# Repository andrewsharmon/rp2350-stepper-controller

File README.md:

# RP2350 coordinated stepper controller

> **Work in progress.** Firmware runs on a Raspberry Pi Pico 2 bench setup.
> The custom board designs are an **unreviewed feasibility first pass**:
> schematics only, no PCB layout, not checked against datasheets or built.
> Don't fabricate them as-is.

A very low-cost, compact controller for up to **10 small stepper motors** (8 mm
micro steppers, 28BYJ-48 converted to bipolar, about 0.2 A per coil or less).
It's aimed at kinetic art first, then lab and robotics use.

There are no stepper-driver ICs. The RP2350 generates sine-PWM microstepping
itself (voltage mode), using PIO state machines fed by DMA, into cheap
DRV8833-class dual H-bridges (AT8833).

## Status

| # | Milestone | State |
|---|---|---|
| 1 | Hardware spec and KiCad schematics for all three boards | first pass, **not reviewed** (open part picks in [hardware/README.md](hardware/README.md)) |
| 2 | One motor: sine PWM via PIO + DMA | done, verified on hardware |
| 3 | 10-axis PWM, ADC monitor, e-stop/button ladder, WS2812 | done on Pico 2; ladder buttons not yet bench-wired |
| 4 | Trajectory generators and profiles, jog modes, telemetry | done (text telemetry; binary framing comes with milestone 5) |
| 5 | Coordinated groups and planner, USB protocol, host tool | done |
| 6 | I²C target, cam/LED shows, flash config, standalone mode | done; I²C target written for the RP2354B board but **untested** (no free pins or I²C master on the bench) |
| 7 | PCB layout, fab, bring-up of the board stack | |

What works today (measured on a Pico 2 + DRV8833 + 8 mm stepper):

- **PWM:** 20 kHz, four-segment H-bridge PWM with slow-decay brake off-time and 1/256-step sine microstepping. Duties below the driver's 0.5 µs minimum pulse are error-diffused.
- **10 axes:** each has its own position, velocity or jog mode on a 1 kHz trajectory tick. Drive amplitude depends on speed, with lower holding current at standstill. Core 1 is about 33-35% loaded, core 0 about 0.5%.
- **Coordinated groups:** up to 4 groups, each owning a set of axes. A group follows a queue of straight lines and arcs in joint space, with every axis starting and finishing together. Lookahead keeps it moving through gentle corners and chord-split arcs, and no axis exceeds its own limits. On the Pico 2, a 300-step-radius circle ran at a constant 800 steps/s and closed exactly.
- **Shows:** keyframe tracks for axes and LED pixels on one timeline, written as JSON, compiled and uploaded to one of 4 flash slots. Axes pass exactly through every keyframe (played as PVT), LED colours fade between keys, and shows can loop. A show is refused if any segment would exceed an axis's speed or acceleration limit. On the Pico 2, a looping 10-axis wave with 9 LED tracks hit all 360 keyframes checked exactly over 2.5 loops.
- **Built-in programs:** 12 looping motion patterns for a row of linear actuators (breathe, travel, standing, ripple, seesaw, zipper, domino, stairs, scan, chase, interference, drift), ±1000 full steps about position 0, all within the default limits (1500 steps/s, 2000 steps/s²). They run along the board's row of connectors, which on single_sh_proto is 5 6 7 8 9 10 1 2 3 4 from the far end to the USB end. They play through the show player as PVT streams, warming up from rest at their first pose. Position 0 is the power-up position, so power up with the actuators mid-stroke (or zero them there with `z`). `prog list`, `prog <n>`, `prog stop` on the console.
- **Standalone mode:** the buttons step through the built-in programs, then the stored shows, with no computer attached. Btn1 clears a latched stop once the e-stop is closed again, or starts / stops the selected entry; Btn2 selects the next one, switching to it if one is playing (the axes stop, then the new one starts). For 1.5 s after a press the axis LEDs show the entry's number as a bar: amber for programs 1-10, cyan for 11-12, magenta for shows. A boot program or show (`boot p<n>` / `boot <n>`, then `save`) starts at power-up.
- **Configuration in flash:** per-axis limits, motion profile, automatic amplitude curve (run low/high, hold, corner speeds) and wiring fixes (reverse direction, swap coils) survive power cycles. Two sectors are written alternately with a generation counter and CRC, so an interrupted save keeps the previous configuration.
- **Streamed PVT:** the host sends position/velocity/time points, and each axis follows a cubic through them. A 10-axis wave streamed at 20 ms per point tracked the ideal curve within 0.0005 steps. Running out of points while moving brakes safely.
- **Telemetry:** up to 1 kHz with selectable axes and fields (position, speed, mode, amplitude, PVT queue, plus motor voltage, ladder, stop state and the last applied command). Each line is numbered so a host can detect drops. Event lines report finished moves, PVT underruns and stops. At 1 kHz with every field on 10 axes, no lines were dropped and core 0 was 39% busy.
- **Electronic cams:** an axis can follow a cam table, so its position is a function of a leader's position: another axis, or one of two virtual leaders with their own speed ramps. Because it's position-based, followers retrace exactly when the leader reverses, at any speed. Cyclic tables can carry a net rise per cycle. Engaging blends in smoothly, and is refused if the follower couldn't keep up at the leader's limits. On the Pico 2, followers matched an independent evaluation of the cam within 0.0013 steps through forward and reverse runs. `save` also stores the loaded cam tables in flash; they are restored at boot.
- **Motion profiles per axis:** `trap`, `scurve` (the default: jerk-limited by a moving average, Tj = 30 ms), `smooth` (two moving averages), `cosine` and `quintic`. Every profile lands exactly on its target within the speed and acceleration limits, and moves can be redirected mid-move without jumps.
- **Safety:** an e-stop or driver fault on the analog ladder cuts all outputs in about 30 µs. A watchdog on core 0 drops outputs to coast if core 1 stalls.
- **Status LEDs:** a WS2812 chain shows overall status plus each axis's speed and direction.

How it works, from trajectory planning to PIO pin toggling: [docs/THEORY.md](docs/THEORY.md).

## Repository layout

```
tools/stepperctl/    host library + command line (binary protocol)
tools/shows/         example shows (JSON; format in tools/stepperctl/show.py)
tools/cams/          example cam tables (JSON: {"cyclic": true, "points": [[x, y], ...]})
tools/pvt_demo.py    host demo: streams a PVT wave over USB serial
tools/web/           browser pages (Web Serial, binary protocol): index.html actuators,
                     tof.html ToF sensor 3D viewer and settings
firmware/            Pico SDK (C) firmware
  third_party/tmf8829/  ams TMF8829 sensor application image (MIT)
  src/               motor PWM (PIO/DMA), microstepping, ADC monitor, ladder, LEDs
  boards/            board header for the custom RP2354B controller
  test/test_host.c   host-side tests (PWM encoder, microstep math, ladder, motion)
  tools/             sine table generator
hardware/            spec, KiCad schematics and BOMs (generated by hardware/gen)
```

## Building the firmware

Requirements:
- [Pico SDK](https://github.com/raspberrypi/pico-sdk) 2.1.1 (set `PICO_SDK_PATH`);
- an `arm-none-eabi` GCC toolchain;
- CMake and Ninja.

```bash
# Custom RP2354B controller (default board)
cmake -S firmware -B firmware/build -G Ninja
cmake --build firmware/build

# single_sh_proto prototype board
cmake -S firmware -B firmware/build-proto -G Ninja -DPICO_BOARD=single_sh_proto
cmake --build firmware/build-proto

# Raspberry Pi Pico 2 bench setup
cmake -S firmware -B firmware/build-pico2 -G Ninja -DPICO_BOARD=pico2
cmake --build firmware/build-pico2
```

Options: `-DNUM_MOTORS=1..10` (default 10), `-DLADDER_BYPASS=ON` (bench without
a ladder wired; never use with motors you can't stop by hand), `-DBOOT_TRACE=ON`.

Flash by copying `stepper.uf2` to the board in BOOTSEL mode, or with picotool:

```bash
picotool load -x firmware/build-pico2/stepper.uf2
```

Host tests (no hardware needed):

```bash
cd firmware/test
cc -std=c11 -O1 -Wall -Wextra -DCONFIG_HOST_TEST -I../src test_host.c ../src/hbridge_encode.c \
   ../src/microstep.c ../src/sine_lut.c ../src/ladder.c ../src/motion.c ../src/group.c \
   ../src/frame.c ../src/config.c ../src/show.c ../src/standalone.c ../src/cam.c ../src/cam_store.c \
   ../src/programs.c ../src/tof_frame.c ../src/tof_map.c -lm -o test_host && ./test_host
```

## ToF sensor (LightRanger 14 Click)

A MikroE LightRanger 14 Click (ams TMF8829 multi-zone dToF, 8x8 to 48x32 zones,
10 mm to 11 m) can hang off the Qwiic port. `tof on` makes I2C1 an I2C host for it
(the I2C target at 0x42 is off meanwhile; `tof off` gives the port back), downloads
the sensor's application into its RAM and loads the 8x8 preset. Driver:
`firmware/src/tmf8829.c`; service and frame streaming: `firmware/src/tof.c`.

Wiring: SDA, SCL, 3V3 and GND from the Qwiic connector. The Click must be set to
I2C, its EN pin (mikroBUS PWM) held high, and it needs 3V3 (bridge JP1
QWIIC_SUPPLY, or power it separately). INT isn't needed: the firmware polls.

`tools/web/tof.html` (Chrome or Edge, opened from file://) connects over USB
serial, switches the sensor on, picks the resolution preset, edits every
register of the configuration page, and draws each measurement as a 3D point
cloud (patches, dots or a surface) and a depth map, with PLY/CSV export. Demo
plays a synthetic scene without a board. From a terminal:

```
tof on            tof res 16         tof period 100     tof start
tof ?             tof get            tof set 0x53 10    tof stop / tof off
```

Not yet run against a real sensor: the register sequences follow ams's reference
driver, and the page was checked with its synthetic frames only.

### ToF map: the sensor drives the actuators

`tof map on` makes the row of linear actuators follow what the sensor sees in a
band across the middle of its field of view (the middle quarter of the rows, the
full width). The band is split left to right into one slice per axis, in the
board's row order (single_sh_proto's connectors run 5 6 7 8 9 10 1 2 3 4 from
the far end to the USB end), and each axis follows the nearest return in its
slice: 150 mm puts it at +1000 full
steps, 300 mm at -1000, and nearer or farther clamps to the ends. A slice with
nothing in it reads as far. Each axis's distance is smoothed (100 ms), and a new
position move goes out when the target changes by 4 steps or more, so the axis's
own limits and profile shape the motion.

Starting switches the sensor on if needed, loads the 16x16 preset, and sets
10 k iterations (the preset's 586 k is for the full range) with a 20 ms period.
Then it measures with no output, unless a host or the console is already
streaming; `tools/web/tof.html` can keep watching. It stops on `tof map off`,
an e-stop, the sensor stopping or failing, a program, show or stress test
starting, or a button starting one. Position 0 is the power-up position, as
for the programs, so power up mid-stroke (or zero there with `z`). The fixed-time
profiles (`cosine`, `quintic`) restart a segment on every retarget; use `scurve`
(the default), `smooth` or `trap`.

```
tof map on            tof map off           tof map ?      (band in zones, live mm and targets)
tof map range 150 300                       tof map steps 1000 -1000    (swap to reverse)
tof map order 1,2,3,4,5,6,7,8,9,10        tof map order board   (axes left to right)
tof map axes 5        tof map mirror on     tof map band 25 100   (height %, width %)
tof map smooth 100    tof map deadband 4    tof map iter 10   tof map period 20   tof map res 16
```

Settings aren't saved to flash yet. On single_sh_proto with the LightRanger 14
and ten actuators it ran at 49 measurements a second (16x16, 10 k iterations,
20 ms), with about 70 of the 256 zones returning; axes under an object at
~210 mm moved to about +150 steps while the rest went to the far end.

## Pico 2 bench setup

| Pico 2 | Connects to |
|---|---|
| GP0-GP3 | motor 1: DRV8833 module AIN1, AIN2, BIN1, BIN2 (motors 2-5 on GP4-GP19) |
| GP20 | WS2812 chain data in (pixel 0 status, pixels 1-10 axes) |
| GP26 | ladder: 10k to 3V3, 20k to GND (idle); see [hardware/README.md](hardware/README.md) |
| GP28 | board ID (optional) |
| VBUS / GND | DRV8833 VM and GND; pull the module's sleep pin (EEP) high |

Motors 6-10 have no pins on the Pico 2, but their state machines and DMA still
run, so the full 10-axis load is exercised.

The USB serial console takes line commands (type `help`). Some examples:

```
m 1 500          move axis 1 to 500 full steps
mr * -100        move every axis back 100 steps
j 3 400          jog axis 3 at 400 steps/s (stops unless repeated within 300 ms)
lim 1 1200 4000  axis 1 limits: 1200 steps/s, 4000 steps/s^2
prof * quintic   minimum-jerk moves on every axis (axes must be at rest)
cam 1 cyclic 0,0 100,40 200,50   cam table 1 (leader x, follower y); +50 per 200-step cycle
vl 1 lim 150 150 virtual leader 1 limits; ce 3 1 v1 makes axis 3 follow cam 1 behind it
vl 1 vel 100     run the virtual leader (negative reverses; followers retrace)
g 1 1,2 800      group 1 = axes 1 and 2, path speed 800 steps/s
gl 1 400 400     group line to (400, 400); ga 1 -300 0 360: full circle around (-300, 0)
p 2 150 300 20   PVT point: axis 2 reaches 150 steps at 300 steps/s, 20 ms after the last
pgo 1,2          start axes 1 and 2 following their queued points on the same tick
t 100            100 telemetry lines/s (header line names the columns)
tf pos,vel,mode  per-axis telemetry fields; ta 1,2 picks axes, ts adds system fields
te on            event lines: E <tick> done <ax> <pos>, underrun, stop, clear
echo off         for scripts: no echo or prompt
drive 1 40 60 25 axis 1 amplitude: 40% at low speed, 60% at high speed, 25% holding
dir 2 rev        reverse axis 2 (coils 2 ba swaps its coils)
cfg / save       show the configuration / write it to flash (axes at rest)
?                status, loads and per-axis table
```

### Host tool (binary protocol)

The same USB port also speaks a framed binary protocol (COBS + CRC-16; the
message spec is [firmware/src/protocol.h](firmware/src/protocol.h)). Frames
and the text console coexist: binary frames are wrapped in 0x00 bytes, which
the console never sends. `tools/stepperctl` is a standard-library Python
client and command line:

```bash
python3 tools/stepperctl ping
python3 tools/stepperctl move 1,2 250 --wait
python3 tools/stepperctl group 1 create 1,2 --feed 800
python3 tools/stepperctl group 1 arc -200 0 360
python3 tools/stepperctl telem --hz 200 --axes 1,2 --seconds 5 > log.csv
python3 tools/stepperctl show upload tools/shows/wave.json --slot 2
python3 tools/stepperctl show run 2          # show list / show stop
python3 tools/stepperctl boot 2 && python3 tools/stepperctl save   # run show 2 at power-up
python3 tools/stepperctl cam load 1 tools/cams/rise_dwell.json
python3 tools/stepperctl cam engage 3 1 v1 && python3 tools/stepperctl vl 1 vel 100
```

```python
from stepperctl import Client          # run from tools/, or put tools/ on sys.path
with Client() as c:
    seq = c.move([1], 500)
    c.wait_settled([1], after=seq)
```

Command-line tool tests (no hardware needed):
`python3 -m unittest discover -s tools/stepperctl -p 'test_*.py' -t tools`

### Browser control page

[tools/web/index.html](tools/web/index.html) drives the actuators from Chrome
or Edge over Web Serial: open the file directly (file:// works) and click
Connect. Each axis gets a position slider (drag to move), hold-to-jog
buttons, →0, Zero and Stop, with live position, speed and amplitude; there
are also an all-axes row, STOP ALL (or Esc), clear stop, manual or automatic
amplitude, speed and acceleration limits, the 12 built-in programs, and the
text console. It speaks the binary protocol on the same USB serial port, so
close any other program that has the port open first.

### I²C (Qwiic) — untested

On the RP2354B board the Qwiic port (I2C1, GPIO 46/47) is an I²C target at
address 0x42 carrying the same requests as the binary protocol, without COBS
framing: write `[type][payload…]`, then read `[n][type][reply payload…]`
(`n` = 0 means not ready yet, read again). See
[firmware/src/i2c_target.h](firmware/src/i2c_target.h). It is compiled out on
the Pico 2 bench build and has not been run on hardware yet.

`tools/pvt_demo.py` streams a travelling wave across every axis as PVT points
(standard-library Python, macOS/Linux):

```bash
tools/pvt_demo.py --amp 200 --hz 0.5 --seconds 15
```

## Notes

- **Sine table:** the SDK's float `sinf` returned wrong values near multiples
  of π/2 on the RP2350, which produced reverse pulses at each coil peak. The
  sine table is generated offline (`firmware/tools/gen_sine_lut.py`), and the
  motion code uses its own polynomials (`firmware/src/trig.h`).
- **Endless DMA:** on the RP2350, endless-mode DMA (`TRANS_COUNT` mode 0xF)
  still needs a non-zero count, or the channel completes immediately.

## License

[MIT](LICENSE), covering both firmware and hardware design files.

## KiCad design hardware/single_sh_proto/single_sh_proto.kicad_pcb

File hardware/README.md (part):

# Hardware specification

> **Status: unreviewed feasibility first pass.** These schematics, part picks
> and pin maps were put together quickly to check that the concept fits. They
> have not been reviewed, checked against datasheets, laid out or built.
> Expect errors; don't fabricate from them as-is.

Low-cost, compact, up-to-10-axis stepper controller for small high-resistance
steppers (8 mm micro steppers, 28BYJ-48 converted to bipolar, <= 0.2 A/coil).
The MCU generates sine PWM (voltage-mode microstepping) directly into cheap
dual H-bridges; there is no stepper-driver IC.

Prefer LCSC / JLCPCB "basic" parts wherever possible. Part picks marked TBD
are open.

## Stack overview

Three boards, 30 x 30 mm core, joined by fine-pitch board-to-board (BTB)
connectors at opposite edges. No screws: the enclosure captures the stack.

| Tier | Board | Layers | Size |
|---|---|---|---|
| 1 | Controller | 4, 1.0 mm thick | 30 x 30 mm |
| 2 | Universal driver | 2 | 30 x 30 mm |
| 3 | Connector / IO (variant-specific) | 2 | sized by connectors, may overhang |

## Tier 1 - Controller

- MCU: **RP2354B** (QFN-80, 48 GPIO, 2 MB in-package flash). Run the ARM cores (FPU).
- 12 MHz crystal, core-regulator inductor and decoupling per the RP2350 hardware design guide.
  - Crystal: Abracon ABM8-272-T3 (C20625731, 10 pF load, ESR <= 50 ohm). The guide's 15 pF / 1 k values are tuned for it; other crystals need retuning and testing.
  - Inductor: Abracon AOTA-B201610S3R3-101-T has a polarity dot. Lay it out in the same orientation as the Pico 2.
- USB-C receptacle with THT shell legs. The enclosure supports the receptacle so plug forces never reach the BTBs.
- CC1 / CC2: 5.1 k pull-downs, also routed to ADC (GPIO40/41) to read the source current advertisement.
- Power path: `VBUS -> PTC (~1.5 A hold, 1812) -> low-Vf Schottky -> V5_IN -> soft-start switch -> V5 bus -> BTB`.
- 3.3 V LDO (ME6211 class, <= 6 V input) fed from V5_IN, ahead of the switch.
- Soft-start: AO3401A P-FET (C15127) with 100 nF gate-source and 100 k gate-ground (tau 10 ms). At plug-in the cap holds the FET off, then it turns on over a few ms, so the ~70 uF on the V5 bus charges at about 0.1 A. USB sees only the ~11 uF on V5_IN at attach. External 5 V (tier 3) reaches V5_IN through the FET's body diode, then its channel.
- 2x Qwiic (JST-SH 4-pin) on I2C1:
  - The board is not powered from Qwiic. The ME6211 conducts from VOUT back to VIN, so a Qwiic-fed 3V3 would back-power the V5 bus (drivers, LEDs).
  - Solder jumpers for pull-ups (2.2-4.7 k) and for supplying 3V3 to downstream Qwiic devices.
- WS2812-class addressable LED on GPIO45. Its DOUT continues down the stack as LED_DATA.
  - Powered from V5 (needs >= 3.7 V). The 3.3 V data goes through a 74AHCT1G125 on V5 to meet VIH = 0.7 VDD.
- Buttons:
  - BOOTSEL (also readable at runtime), TS-1187A, right edge below connector B. The single boards use the TS-1088-AR02016 instead (same part as Btn1/Btn2).
  - Btn1 and Btn2 on the analog ladder (see below): XUNPU TS-1088-AR02016 (C720477, 3.9 x 3.0 mm, 2 pads), stacked in the top-right corner. They started over the BTB headers for rigidity, but their pads blocked the connector fan-out, so the case should support the board under them.
- SWD test pads.

## Tier 2 - Universal driver

- 10x **AT8833CQ** (Zhongkewei, LCSC C5120769, QFN-16 4 x 4).
  - DRV8833-compatible logic: 00 coast, 01 reverse, 10 forward, 11 brake.
  - VM 2.7-15 V, UVLO <= 2.5 V, 1.0 A RMS. Inputs have 100 k pull-downs.
  - Second source: JSMSEMI DRV8833RTYR / JSM8833RTYR (same QFN-16 4 x 4). Verify its pinout against TI DRV8833RTY before relying on it.
- Passives per chip:
  - AISEN / BISEN: 0.68-1 ohm to ground. Above I = 0.2 V / R (Vtrip 160-240 mV) the chip chops the current in slow decay; it does not report a fault. With 1 ohm that is 0.16-0.24 A. Give it a separate return to the star ground.
  - VCP: 0.1 uF to VM.
  - VINT: 1 uF.
  - These are the AT8833 datasheet values. TI's DRV8833 uses 0.01 uF and 2.2 uF, so don't copy from it.
  - VM: 1-2.2 uF ceramic at the pin.
- Shared bulk: 2-4x 10 uF 0805 spread over the V5 pour.
- nSLEEP: pulled high through 20-75 k (always awake, <= 3.5 mA idle per chip).
- nFAULT (open drain): wire-OR all chips onto the LADDER line.
- VMOTOR is the V5 bus directly.
- VMOTOR_SENSE: 1:5 divider to GPIO42.

AT8833CQ QFN-16 pinout: 1 AISEN, 2 AOUT2, 3 BOUT2, 4 BISEN, 5 BOUT1, 6 nFAULT,
7 BIN1, 8 BIN2, 9 VCP, 10 VM, 11 GND, 12 VINT, 13 AIN2, 14 AIN1, 15 nSLEEP,
16 AOUT1, plus the exposed pad to GND.

## Tier 3 - Connector / IO

- Motor connectors per variant. Each uses the motor's stock plug:
  - `io_xh`, 28BYJ-48: one JST-XH 5-pin (B5B-XH-A, C157991) per motor, ten total.
    - Pins: 1 blue, 2 pink, 3 yellow, 4 orange. Pin 5 (red centre tap) is not connected after the bipolar mod.
    - Coils: A = pins 1/3, B = pins 2/4.
  - `io_sh`, dual 8 mm micro steppers: one JST-SH 8-pin (BM08B-SRSS-TB, C160394) per motor pair, five total.
    - Pins 1-4 = first motor (A1 A2 B1 B2), pins 5-8 = second motor.
  - Firmware remaps coil order and polarity per axis, so lead-colour variations can be fixed in software.
- Optional external 5 V input -> Schottky -> V5 bus. This powers everything without USB.
- LED strip output (V5 / DATA / GND):
  - Data: 74AHCT1G125 buffer (powered from V5), then a 33-100 ohm series resistor.
  - Strip power, chosen by footprint: shared V5 through a polyfuse, or a separate LED power input.
- E-stop jack and panel buttons, in parallel with the ladder.
- Board ID: one resistor to GND, read through the controller pull-up on GPIO43. See the board-ID table below.

## Interconnect (BTB)

- **Part:** Hirose DF40, 0.4 mm pitch, 40 pins, **2.0 mm stack height**:
  - **Header** DF40C-40DP-0.4V(51) (C424643). Goes on the **underside of the upper board**. The header is the same for every DF40 stack height.
  - **Socket** DF40C(2.0)-40DS-0.4V(51) (C597934). Goes on the **top of the lower board**. The socket sets the stack height.
  - Rated 0.3 A per contact. The four corner contacts (pins 1, 2, 39, 40) are metal fittings per Hirose (catalogue note 3): they are soldered for strength but left unconnected, leaving 36 usable pins.
  - The 2.0 mm stack leaves room between boards for low parts (0402 passives, QFNs, SOT-23) on the facing sides. Keep anything taller than ~1 mm off them, and don't put a part opposite another one on the facing board if the two heights add up to more than ~1.7 mm.
- **Footprints** are in `lib/stack.pretty`, generated by `gen/footprints.py` from the DF40 catalogue's recommended layouts:
  - Socket: 0.20 x 0.70 pads (rows 2.38-3.78 mm across), plus the 1.5 mm layout-prohibited strip between the rows as a copper keepout.
  - Header: 0.23 x 0.66 pads (rows 2.05-3.37 mm across), plus 0.35 mm metal-fitting tabs 0.30-0.65 mm beyond each row end.
  - Pin 1 at -X. The socket's odd row is at -Y; the header's is drawn at +Y, so after the flip onto the underside header pin n sits over socket pin n. Still check it in the 3D viewer before ordering.
- **Not polarized** (Hirose note 5). Two connectors per interface at offset positions key the stack so the boards only mate one way: A is 2 mm below the board centre line, B on it.
- BTB pins carry roughly 0.3-0.5 A each.
- The authoritative pin lists are `btb_a()` and `btb_b()` in `gen/build.py`.

| Connector | Controller <-> driver | Driver <-> tier 3 |
|---|---|---|
| A | motors 1-7 inputs (28), 4x V5, 3x GND, 3V3, 4 corner NC | motors 1-7 outputs (28), 4x V5, 4x GND, 4 corner NC |
| B | motors 8-10 inputs (12), LED_DATA, LADDER, BOARD_ID, VMOT_SENSE, 9x V5, 11x GND, 4 corner NC | motors 8-10 outputs (12), LED_DATA, LADDER, BOARD_ID, 9x V5, 12x GND, 4 corner NC |

Pin order follows the MCU's pin order, so the controller's traces fan in without crossing. Connectors are placed pin 1 at the top: A down the left edge (power, then M1 from the MCU's top-left corner, M2-M5 down its left side, M6-M7 round its bottom-left), B down the right edge (utilities, then M10, M9, M8). M6/M7 are on A so they don't cross the crystal and SWD pins on the MCU's bottom side. The driver board shares V5 between both connectors, so the uneven V5 split doesn't matter. The driver's sockets copy the controller headers' positions and rotation.

**Board ID:** the 10 k 1% pull-up to 3V3 is on the controller. Each tier-3 variant fits one resistor to GND, 5% is fine. With no tier 3 attached, the line reads 3.3 V.

The values are common 0402 parts. Ranges are worst case for a 5% ID resistor and the 1% pull-up; adjacent levels stay at least 249 mV apart, and the thresholds sit midway between ranges.

| ID resistor | Nominal | Range (mV) | Threshold above (mV) | Board |
|---|---|---|---|---|
| 0 ohm | 0 mV | 0 | 150 | |
| 1 k | 300 mV | 284-316 | 440 | |
| 2.2 k | 595 mV | 566-624 | 820 | |
| 4.7 k | 1055 mV | 1012-1098 | 1350 | io_sh (dual 8 mm micro steppers) |
| 10 k | 1650 mV | 1599-1699 | 1960 | io_xh (28BYJ-48) |
| 22 k | 2269 mV | 2225-2310 | 2500 | |
| 47 k | 2721 mV | 2691-2749 | 3020 | |
| not fitted | 3300 mV | 3300 | - | no tier 3 attached |

## GPIO map (RP2354B)

| GPIO | Function |
|---|---|
| 0-39 | Motor n (1-10) on GPIO 4(n-1)..4(n-1)+3 = AIN1 AIN2 BIN1 BIN2 |
| 40 | USB-C CC1 (ADC0) |
| 41 | USB-C CC2 (ADC1) |
| 42 | VMOTOR_SENSE, 1:5 (ADC2). Can't tell external power from USB (both feed V5 through Schottkys) |
| 43 | Tier-3 board ID (ADC3) |
| 44 | Ladder (ADC4) |
| 45 | WS2812 data |
| 46 | Qwiic SDA (I2C1) |
| 47 | Qwiic SCL (I2C1) |

PIO allocation:

| PIO block | State machines | Use |
|---|---|---|
| PIO0 | SM0-3 | Motors 1-4 |
| PIO1 | SM0-3 | Motors 5-8 |
| PIO2 (GPIOBASE = 16) | SM0-1 | Motors 9-10 |
| PIO2 | SM2 | WS2812 |
| PIO2 | SM3 | Spare |

Use external pull-ups on all inputs on A2 silicon (RP2350-E9 erratum; fixed from A3).

## Ladder on GPIO44

```
3V3 --[10k]--+---------> GPIO44 (ADC4), 100 nF to GND
             |-- E-stop (NC) --[20k]-- GND   (solder jumper bypass when no e-stop)
             |-- Btn1 ---------[10k]-- GND
             |-- Btn2 ---------[3.3k]- GND
             '-- nFAULT (open drain, all drivers)
```

| Condition | Voltage | Meaning |
|---|---|---|
| E-stop open or cable cut | 3.3 V | STOP |
| Idle | ~2.2 V | normal |
| Btn1 | ~1.3 V | user 1 |
| Btn2 | ~0.7 V | user 2 |
| nFAULT | ~0 V | driver fault, STOP |

Use 1% resistors. Thresholds sit midway between the levels; debounce over 2-3 samples.

A held button hides an open e-stop (e-stop open + Btn1 = 1.65 V, + Btn2 = 0.82 V). Firmware latches a stop on 1.49-1.76 V held 5 ms, or on any button held over 3 s; see `firmware/src/ladder.h`.

## Electrical notes

- PWM frequency is about 20 kHz. The AT8833 input deglitch (about 450 ns) sets a minimum pulse of about 0.5 us, roughly 1% duty. Firmware dithers duties below that.
- Wait about 100 ms after power-up before energizing motors (V5 soft-start settling).
- USB budget comes from CC; brownout guard from VMOTOR_SENSE.
- RP2350-E9 (a GPIO with its input buffer on can sit near 2.2 V, which the AT8833's >= 2 V VIH reads as high) needs no hardware fix on the motor inputs. It is fixed in silicon from A3 (A4 is the production stepping; order A4). On A2 it can't occur after a power-on or RUN reset (input enable starts clear), and the firmware turns the motor pins' input buffers off (they are never read), so they stay off across a watchdog reset whether or not it resets the pads. The AT8833's 100 k pull-downs are enough.
- Tier 3: the NO_ESTOP jumper ships bridged. It must be cut when an e-stop is fitted, or the e-stop does nothing. Mark this on the silkscreen.

## Single board (`single_sh`)

Controller, driver and the `io_sh` connectors on one PCB, from the `single_sh/` schematic (`single()` in `gen/build.py`). Fully routed: 0 unconnected, no DRC errors, schematic parity clean.

- Schematic: a wired, hierarchical drawing (`gen/single_sh_sch.py`), unlike the label-only stack schematics.
  - Sheets: overview, power and USB, MCU, motor drivers, connectors and UI. Each block is framed, with design notes on its sheet.
  - Inter-sheet signals (motor lines, LADDER, BOARD_ID, I2C, CC, USB) are global labels. Power rails are power symbols, so their PCB nets are `GND`, `+3V3`, `V5` and so on; nets local to a sheet are named `/<sheet>/<label>`, e.g. `/Power/V5_IN`.
  - The AT8833 uses a project symbol (`lib/stack.kicad_sym`, written by `build.py`) with the DRV8833RTY pin numbers, laid out for the drawing; VINT is typed as an output, so it needs no PWR_FLAG.

- **122 x 20 mm**, 4 layers, 1.6 mm thick. All parts on top; only the THT legs of the USB-C and the JST-PH/XH connectors come through.
- Layers: F.Cu parts and signals, In1 solid GND, In2 V5, B.Cu signals. In2 has a 3V3 island under the MCU, joined to the LDO by a thin finger along the -y edge.
- Along the board: USB-C (mouth on the short edge) and power path | drivers M4 M3 M2 M1 | MCU | drivers M10 M9 M8 M7 M6 M5 | LED strip connector.
  - Motor connectors run along one long edge in the order J12 J11 | J15 J14 J13, so each motor bus leaves the MCU in pin order and never crosses itself.
  - Qwiic x2, BOOTSEL, e-stop, panel buttons, 5 V in, status LED and LED power run along the other long edge, above the drivers.
- Driver cell: AT8833 rotated so its outputs face the connector. VINT/VM/VCP caps sit above it; the 0603 sense resistors sit below, ISEN pads inboard, each GND pad with its own via (R16 and R20 instead tie to the neighbouring cell's GND pad).
  - BOUT2 runs down between the two ISEN pads and BOUT1 under R_B's body. The resistors went 0805 -> 0603 in place on the routed board: pad 1 (ISEN) kept, GND pad 0.275 mm inboard (R5 and R11 keep the GND pad instead, clear of a neighbouring via and track).
  - The connector's pin order (B2 B1 A2 A1, left to right) runs against the driver's (A1 A2 B2 B1), so A1/A2 hop over B1/B2 on short In2 jumpers (4 vias per motor).
  - Swapping this board's connector pin assignment (pins 1-2 = coil B, pins 3-4 = coil A reversed) would remove the jumpers, if firmware maps coil order and polarity per board. Not done, because the cable pinout would then differ from `io_sh`.
- V5 enters the In2 plane through via clusters at the soft-start FET, the external 5 V diode and the LED-strip fuse.
- Layout source: `single_sh()` in `gen/pcbgen.py` (placement and zones).
  - The driver cells and the core regulator were pre-routed by script. The rest was routed with Freerouting 2.5.0 plus a small grid router.
  - Those routing scripts are not in the repo; the board is hand-edited from here.
- Silkscreen: reference designators are hidden (too dense).
  - Motor numbers sit above each connector; function labels are on top where they fit, otherwise on the underside.
  - The underside also carries the NO_ESTOP cut warning.
  - The 4 remaining silkscreen warnings are outlines touching each other or the board edge.

### Fabrication (JLCPCB)

`gen/jlcfab.py` writes the order files to `single_sh/jlcpcb/`: Gerbers + Excellon drill (zipped), the BOM and the placement (CPL) file. Run it with KiCad's Python; `--check` also verifies the placements.

```bash
/Applications/KiCad/KiCad.app/Contents/Frameworks/Python.framework/Versions/Current/bin/python3 gen/jlcfab.py single_sh --check
```

- JLCPCB places each part with its own library footprint, so `CPL_FIX` corrects rotation and origin per LCSC part (SOT-23, SOT-23-5, WS2812, the JST connectors and USB-C need it).
  - `--check` fetches those footprints from the JLCEDA library and compares their pads with the KiCad pads.
  - All 142 placements land within 0.003 mm of centre with every pin on its own pad.
- Pin numbering traps:
  - SS54 (C22452): JLCPCB numbers 1 = anode, 2 = cathode, the reverse of KiCad's diodes. `PAD_MAP` handles it; the diodes need no extra rotation.
  - AOTA inductor (L1): the dot goes at the +1V1 end, as on the Pico 2 (RP2350 datasheet, regulator layout figure). JLCPCB's silkscreen and Abracon's top view put the dot at their pad 2, so pad 2 lands on +1V1. JLCPCB's placement preview shows the dot there; the order remark repeats it.
- The BOM has one line per LCSC part. JLCPCB unticks a part that appears on several lines.
- First order (2026-10-07, 10 boards, $314 before shipping):
  - PCB: 4 layers, 1.6 mm, ENIG (0.4 mm pitch QFN-80), min via 0.15/0.3 mm, plugged vias.
  - Assembly: Standard PCBA, top side, confirm parts placement with no auto-confirm.
- Cost drivers:
  - The 0.15 mm via option ($37) forces a 4-wire Kelvin test ($18) and TG155.
  - The WS2812B-2020 (D2) is Standard-PCBA only, as are its alternatives. Standard adds $25 setup, feeder fees and 5 mm edge rails (a 122 x 70 mm panel, nearly double the shipping weight). Economic with D2 left off was $265.
  - THT parts (JST PH/XH, the USB-C shell legs) are hand soldered, about $6.
- Vias sit in the QFN exposed pads and in U11 pin 59 (+3V3). JLCPCB doesn't offer tented for this board; plugged (solder mask) is the free option. Epoxy filled & capped costs about $20 more if those joints give trouble.

## Prototype single board (`single_sh_proto`)

Same circuit as `single_sh`, re-made for cheaper fabrication. Started 2026-10-10. Fully routed, DRC and schematic parity clean, and JLCDFM shows no "danger" items (2026-10-11; re-check after the 5050 LED change); unreviewed.

Bring-up (2026-10-21, board 1): boots, flashes over USB and runs the firmware; status readings, nested-pinout config, status LED and buttons check out. Motors not tested yet. Results in [`docs/BRINGUP_single_sh_proto.md`](../docs/BRINGUP_single_sh_proto.md#record).

- Every passive is 0603 and a JLCPCB basic part (`PASSIVES` in `gen/build.py`, applied by `single(..., proto=True)`).
  - 10 uF bulk caps go 0805 -> 0603 (10 V X5R, C19702) on the 5 V rail.
  - USB series resistors are 22 ohm (C23345): 27 ohm 0603 is extended.
  - L1: the Abracon AOTA-B201610S3R3-101-T had 4 in stock at JLCPCB (2026-10-11), so this board uses CMLW201610S3R3MST (C411344, 3.3 uH, 245 mohm, 1.05 A sat, shielded, 2016). Not the part Raspberry Pi validated for the core regulator: check the 1V1 ripple on the first boards. No polarity mark; JLCPCB numbers its pads the other way round (`PAD_MAP` in `gen/jlcfab.py`).
- Status LED D2 is the 5050 XINGLIGHT XL-5050RGBC-2812B (C2843785, 720k in stock 2026-10-11) instead of the 2020: JLCPCB lists the 2020 as Standard-PCBA only, and this board orders Economic. Same WS2812 protocol and data path; J6 moved 2.6 mm right to make room, D2's courtyard trimmed to 0.05 mm round its pads (the library one overlaps U14's).
- Motor connectors use the corrected dual-motor cable pinout (one motor's coils on the outer pins, the other's on the inner ones), `sh_motor_pair_nested()` in `gen/build.py`. Coil order and polarity are chosen so the drivers' outputs reach the pins without crossing:

  | Pin | 1 | 2 | 3 | 4 | 5 | 6 | 7 | 8 |
  |---|---|---|---|---|---|---|---|---|
  | J11 | M2 A1 | M2 A2 | M1 B1 | M1 B2 | M1 A2 | M1 A1 | M2 B1 | M2 B2 |

  J12-J15 follow the same pattern (M4+M3, M6+M5, M8+M7, M10+M9). The even motor is the cable's outer motor; the odd (inner) motor has its coils swapped and coil A reversed, so its axis needs `CONFIG_FLAG_SWAP_COILS` (and `CONFIG_FLAG_REVERSE` for the same direction) in firmware. `single_sh` and `io_sh` still use the old pinout.
- Bring-up test pads TP6-TP17 (supplies on top: VBUS, V5IN, V5, GND, VMOT, SDA; signals underneath: 1V1, LADDER, NSLP, SCL, LED, GND), labelled on the silkscreen; placed by `gen/add_testpoints.py`. TP1-TP5 (SWD, RUN, GND, 3V3) as on single_sh.
- Back silkscreen: a squid whose ten tentacles reach the ten motor drivers, and "ASH+C 2026" (`gen/squid_silk.py`, re-run after any layout change). Reference designators are hidden.
- **150 x 30 mm**, 4 layers, 1.6 mm: F.Cu / B.Cu signals, In1 solid GND, In2 V5 with a 3V3 island round the MCU and a +1V1 area under its body. Same linear arrangement as single_sh: USB-C and power | M4-M1 | MCU | M10-M5 | LED strip.
  - USB-C shell slots 0.1 mm wider than the library footprint, pads grown to keep a 0.2 mm ring.
- Layout rules (all built into the generator and routing scripts):
  - Vias 0.52 mm pad / 0.3 mm drill (JLCPCB's no-extra-cost 0.3 mm via class; 0.11 mm annular ring, since JLCDFM flags 0.1 mm and under). 0.1 mm copper clearance; plane zones 0.2 mm.
  - Traces straight or at 45 degrees only, entering pads on their centre line and no wider than the pad.
  - No vias in pads (except the thermal vias in the AT8833 and RP2354B exposed pads), and every via at least 0.1 mm from any pad, same net included.
- Layout source: `single_sh_proto()` in `gen/pcbgen.py`.
  - Driver cells: VINT / VM / VCP caps stand vertically 4.75 mm above each AT8833, leaving room for pin 10's V5 via; pin 11 runs into the exposed pad. A pair's drivers sit 7.5 mm apart, pairs 16 mm. Sense resistors' ISEN pads sit straight below the chip's ISEN pins.
  - MCU decoupling 2.6 mm out from the pins. Crystal above the MCU's +x corner, test pads along the bottom edge, so the +x face is left to the M5-M10 input buses.
- Routing (scripts not in the repo; recipe as for single_sh): driver cells pre-routed by script, Freerouting 2.5.0 (45-degree mode, no vias on SMD pads) for the bulk, a small grid router for the last few, then clean-up passes for pad entries and 45-degree segments.
  - Each pair: the left (outer-motor) driver takes its B outputs straight down on F.Cu and hops its A outputs over the other driver on In2, to vias just below the connector pads. The right (inner-motor) driver fans all four outputs left on F.Cu in nested L's.
  - LADDER (nFAULT wire-OR): B.Cu drops to a spine under the driver row, one per side. NSLEEP: In2 risers to vias above the cap row; In2 links only join one pair to the next (a link across a pair would cut the In2 V5 pour round the outer driver's caps off from the plane).
  - The four +1V1 MCU pins each drop to a via into the In2 +1V1 area under the chip.
- Firmware: `-DPICO_BOARD=single_sh_proto`. Bring-up checklist: [`docs/BRINGUP_single_sh_proto.md`](../docs/BRINGUP_single_sh_proto.md).
- Fabrication: `gen/jlcfab.py single_sh_proto --check` writes `single_sh_proto/jlcpcb/` (142 placements, 36 BOM lines: 21 basic, 15 extended; Economic PCBA; every placement checked against JLCPCB's footprints). Order: 4 layers, 1.6 mm, ENIG, plugged vias, 0.3 mm min via hole.

## Schematics and BOM

Schematics are generated. Edit `gen/build.py`, not the `.kicad_sch` files. For `single_sh`, part placement and wiring live in `gen/single_sh_sch.py`.

```bash
python3 gen/footprints.py   # project footprints -> lib/stack.pretty
python3 gen/build.py        # schematics
```

The controller and `single_sh` PCBs were started by `gen/pcbgen.py <board>`, run once with KiCad's Python
(it needs `pcbnew`); it refuses to overwrite an existing board. It set up the
outline, stackup, JLCPCB rules and net classes, and a first placement of every
part. From there the layout is edited by hand in KiCad.

```bash
/Applications/KiCad/KiCad.app/Contents/Frameworks/Python.framework/Versions/Current/bin/python3 gen/pcbgen.py controller
```

Outputs:

- `controller/`, `driver/`, `io_xh/` (28BYJ-48), `io_sh/` (micro steppers): one KiCad schematic each.
- `single_xh/`, `single_sh/`: the whole circuit (controller + driver + that IO variant) on one board, with the BTB connectors removed and their nets joined directly. `single_sh` has a routed PCB (see above); `single_xh` is schematic only.
- Each part's pins are connected by net labels, except in `single_sh`, which is drawn with wires (`gen/single_sh_sch.py`, using `gen/schdraw.py`).
  - Before writing, `schdraw` traces the drawing the way KiCad does (wires, junctions, labels, power symbols) and fails unless every pin is on exactly the net `build.py` gave it.
  - Moving or adding a part in `build.py` means placing it in `single_sh_sch.py` too; an unplaced part, unwired pin or short stops the build.
  - Refs and symbol UUIDs are what the routed PCB links to. Changing a net's name or sheet changes its PCB net name: run Update PCB from Schematic in KiCad afterwards.
- `*_bom.csv` in each folder, exported with `kicad-cli sch export bom` (grouped by value, footprint, LCSC, MPN and note).

Part data:

- Every BOM line has an LCSC number, checked against the JLCPCB parts library on 2026-10-07 (part, package, rating, stock). Passives take theirs from `PASSIVES` in `gen/build.py`.
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
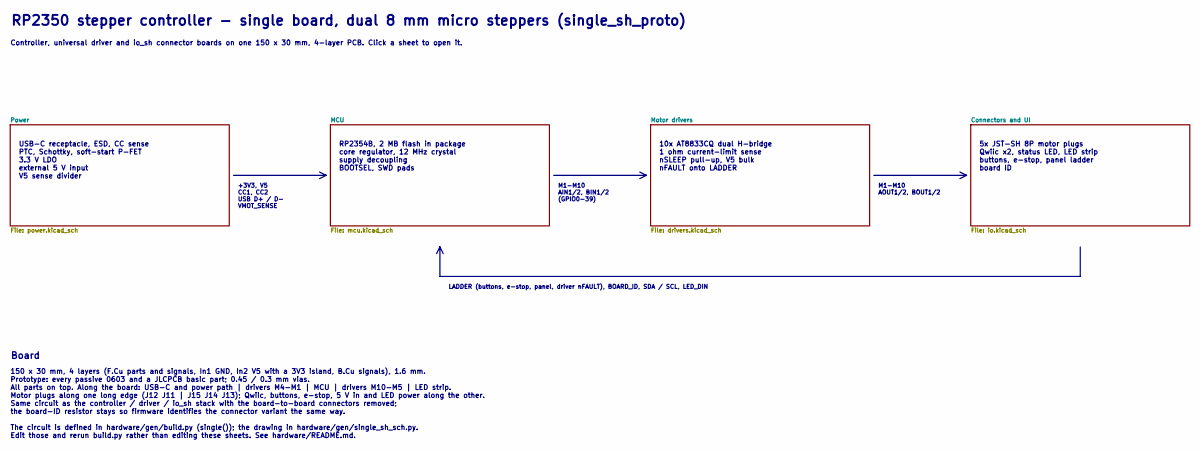
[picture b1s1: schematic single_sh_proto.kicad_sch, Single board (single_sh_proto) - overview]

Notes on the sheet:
RP2350 stepper controller - single board, dual 8 mm micro steppers (single_sh_proto)
Controller, universal driver and io_sh connector boards on one 150 x 30 mm, 4-layer PCB. Click a sheet to open it.
USB-C receptacle, ESD, CC sense PTC, Schottky, soft-start P-FET 3.3 V LDO external 5 V input V5 sense divider
RP2354B, 2 MB flash in package core regulator, 12 MHz crystal supply decoupling BOOTSEL, SWD pads
10x AT8833CQ dual H-bridge 1 ohm current-limit sense nSLEEP pull-up, V5 bulk nFAULT onto LADDER
5x JST-SH 8P motor plugs Qwiic x2, status LED, LED strip buttons, e-stop, panel ladder board ID
+3V3, V5 CC1, CC2 USB D+ / D- VMOT_SENSE
M1-M10 AIN1/2, BIN1/2 (GPIO0-39)
M1-M10 AOUT1/2, BOUT1/2
LADDER (buttons, e-stop, panel, driver nFAULT), BOARD_ID, SDA / SCL, LED_DIN
Board
150 x 30 mm, 4 layers (F.Cu parts and signals, In1 GND, In2 V5 with a 3V3 island, B.Cu signals), 1.6 mm. Prototype: every passive 0603 and a JLCPCB basic part; 0.45 / 0.3 mm vias. All parts on top. Along the board: USB-C and power path | drivers M4-M1 | MCU | drivers M10-M5 | LED strip. Motor plugs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

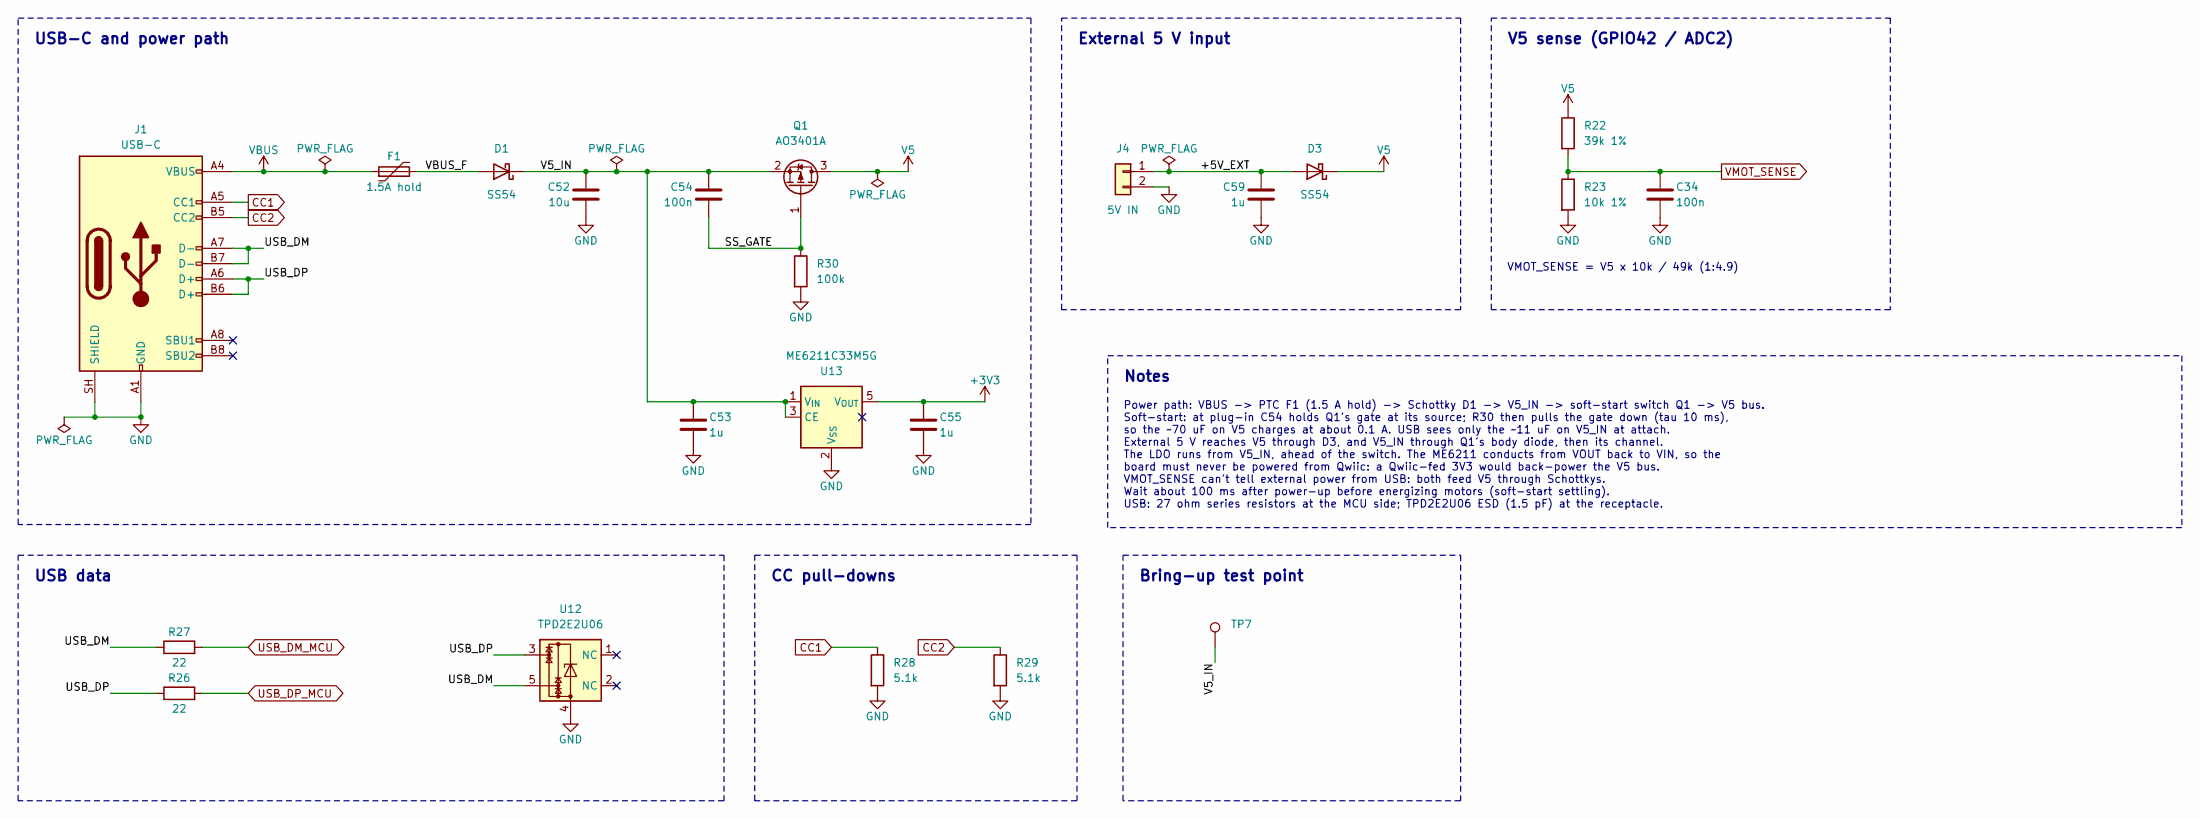
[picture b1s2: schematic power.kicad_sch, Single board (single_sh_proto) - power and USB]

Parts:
C34, C54: 100n; C_0603_1608Metric; MPN CC0603KRX7R9BB104; LCSC C14663
C52: 10u; C_0603_1608Metric; MPN CL10A106KP8NNNC; LCSC C19702
C53, C55, C59: 1u; C_0603_1608Metric; MPN CL10A105KB8NNNC; LCSC C15849
D1, D3: SS54; D_SMA; MPN SS54; LCSC C22452
F1: 1.5A hold; Fuse_1812_4532Metric; MPN SMD1812P150TF/8; LCSC C209721
J1: USB-C; USB_C_Receptacle_HRO_TYPE-C-31-M-12; MPN TYPE-C-31-M-12; LCSC C165948
J4: 5V IN; JST_PH_B2B-PH-K_1x02_P2.00mm_Vertical; MPN B2B-PH-K-S; LCSC C131337
Q1: AO3401A; SOT-23; MPN AO3401A; LCSC C15127
R22: 39k 1%; R_0603_1608Metric; MPN 0603WAF3902T5E; LCSC C23153
R23: 10k 1%; R_0603_1608Metric; MPN 0603WAF1002T5E; LCSC C25804
R26, R27: 22; R_0603_1608Metric; MPN 0603WAF220JT5E; LCSC C23345
R28, R29: 5.1k; R_0603_1608Metric; MPN 0603WAF5101T5E; LCSC C23186
R30: 100k; R_0603_1608Metric; MPN 0603WAF1003T5E; LCSC C25803
TP7: V5_IN; TestPoint_Pad_D1.0mm
U12: TPD2E2U06; SOT-553; MPN TPD2E2U06DRLR; LCSC C1972959
U13: ME6211C33M5G; SOT-23-5; MPN ME6211C33M5G-N; LCSC C82942

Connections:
+3V3: C55.1, U13.5 (V_{OUT}); also elsewhere on the board
/Power/+5V_EXT: C59.1, D3.2 (A), J4.1
/Power/SS_GATE: C54.2, Q1.1 (G), R30.1
/Power/USB_DM: J1.A7 (D-), J1.B7 (D-), R27.1, U12.5
/Power/USB_DP: J1.A6 (D+), J1.B6 (D+), R26.1, U12.3
/Power/V5_IN: C52.1, C53.1, C54.1, D1.1 (K), Q1.2 (S), TP7.1, U13.1 (V_{IN}), U13.3 (CE)
/Power/VBUS_F: D1.2 (A), F1.2
CC1: J1.A5 (CC1), R28.1; also elsewhere on the board
CC2: J1.B5 (CC2), R29.1; also elsewhere on the board
GND: C34.2, C52.2, C53.2, C55.2, C59.2, J1.A1 (GND), J1.A12 (GND), J1.B1 (GND), J1.B12 (GND), J1.SH (SHIELD), J4.2, R23.2, R28.2, R29.2, R30.2, U12.4, U13.2 (V_{SS}); also elsewhere on the board
USB_DM_MCU: R27.2; also elsewhere on the board
USB_DP_MCU: R26.2; also elsewhere on the board
V5: D3.1 (K), Q1.3 (D), R22.1; also elsewhere on the board
VBUS: F1.1, J1.A4 (VBUS), J1.A9 (VBUS), J1.B4 (VBUS), J1.B9 (VBUS); also elsewhere on the board
VMOT_SENSE: C34.1, R22.2, R23.1; also elsewhere on the board

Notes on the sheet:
USB-C and power path
USB data
CC pull-downs
External 5 V input
V5 sense (GPIO42 / ADC2)
VMOT_SENSE = V5 x 10k / 49k (1:4.9)
Notes
Power path: VBUS -> PTC F1 (1.5 A hold) -> Schottky D1 -> V5_IN -> soft-start switch Q1 -> V5 bus. Soft-start: at plug-in C54 holds Q1's gate at its source; R30 then pulls the gate down (tau 10 ms), so the ~70 uF on V5 charges at about 0.1 A. USB sees only the ~11 uF on V5_IN at attach. External 5 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
Bring-up test point

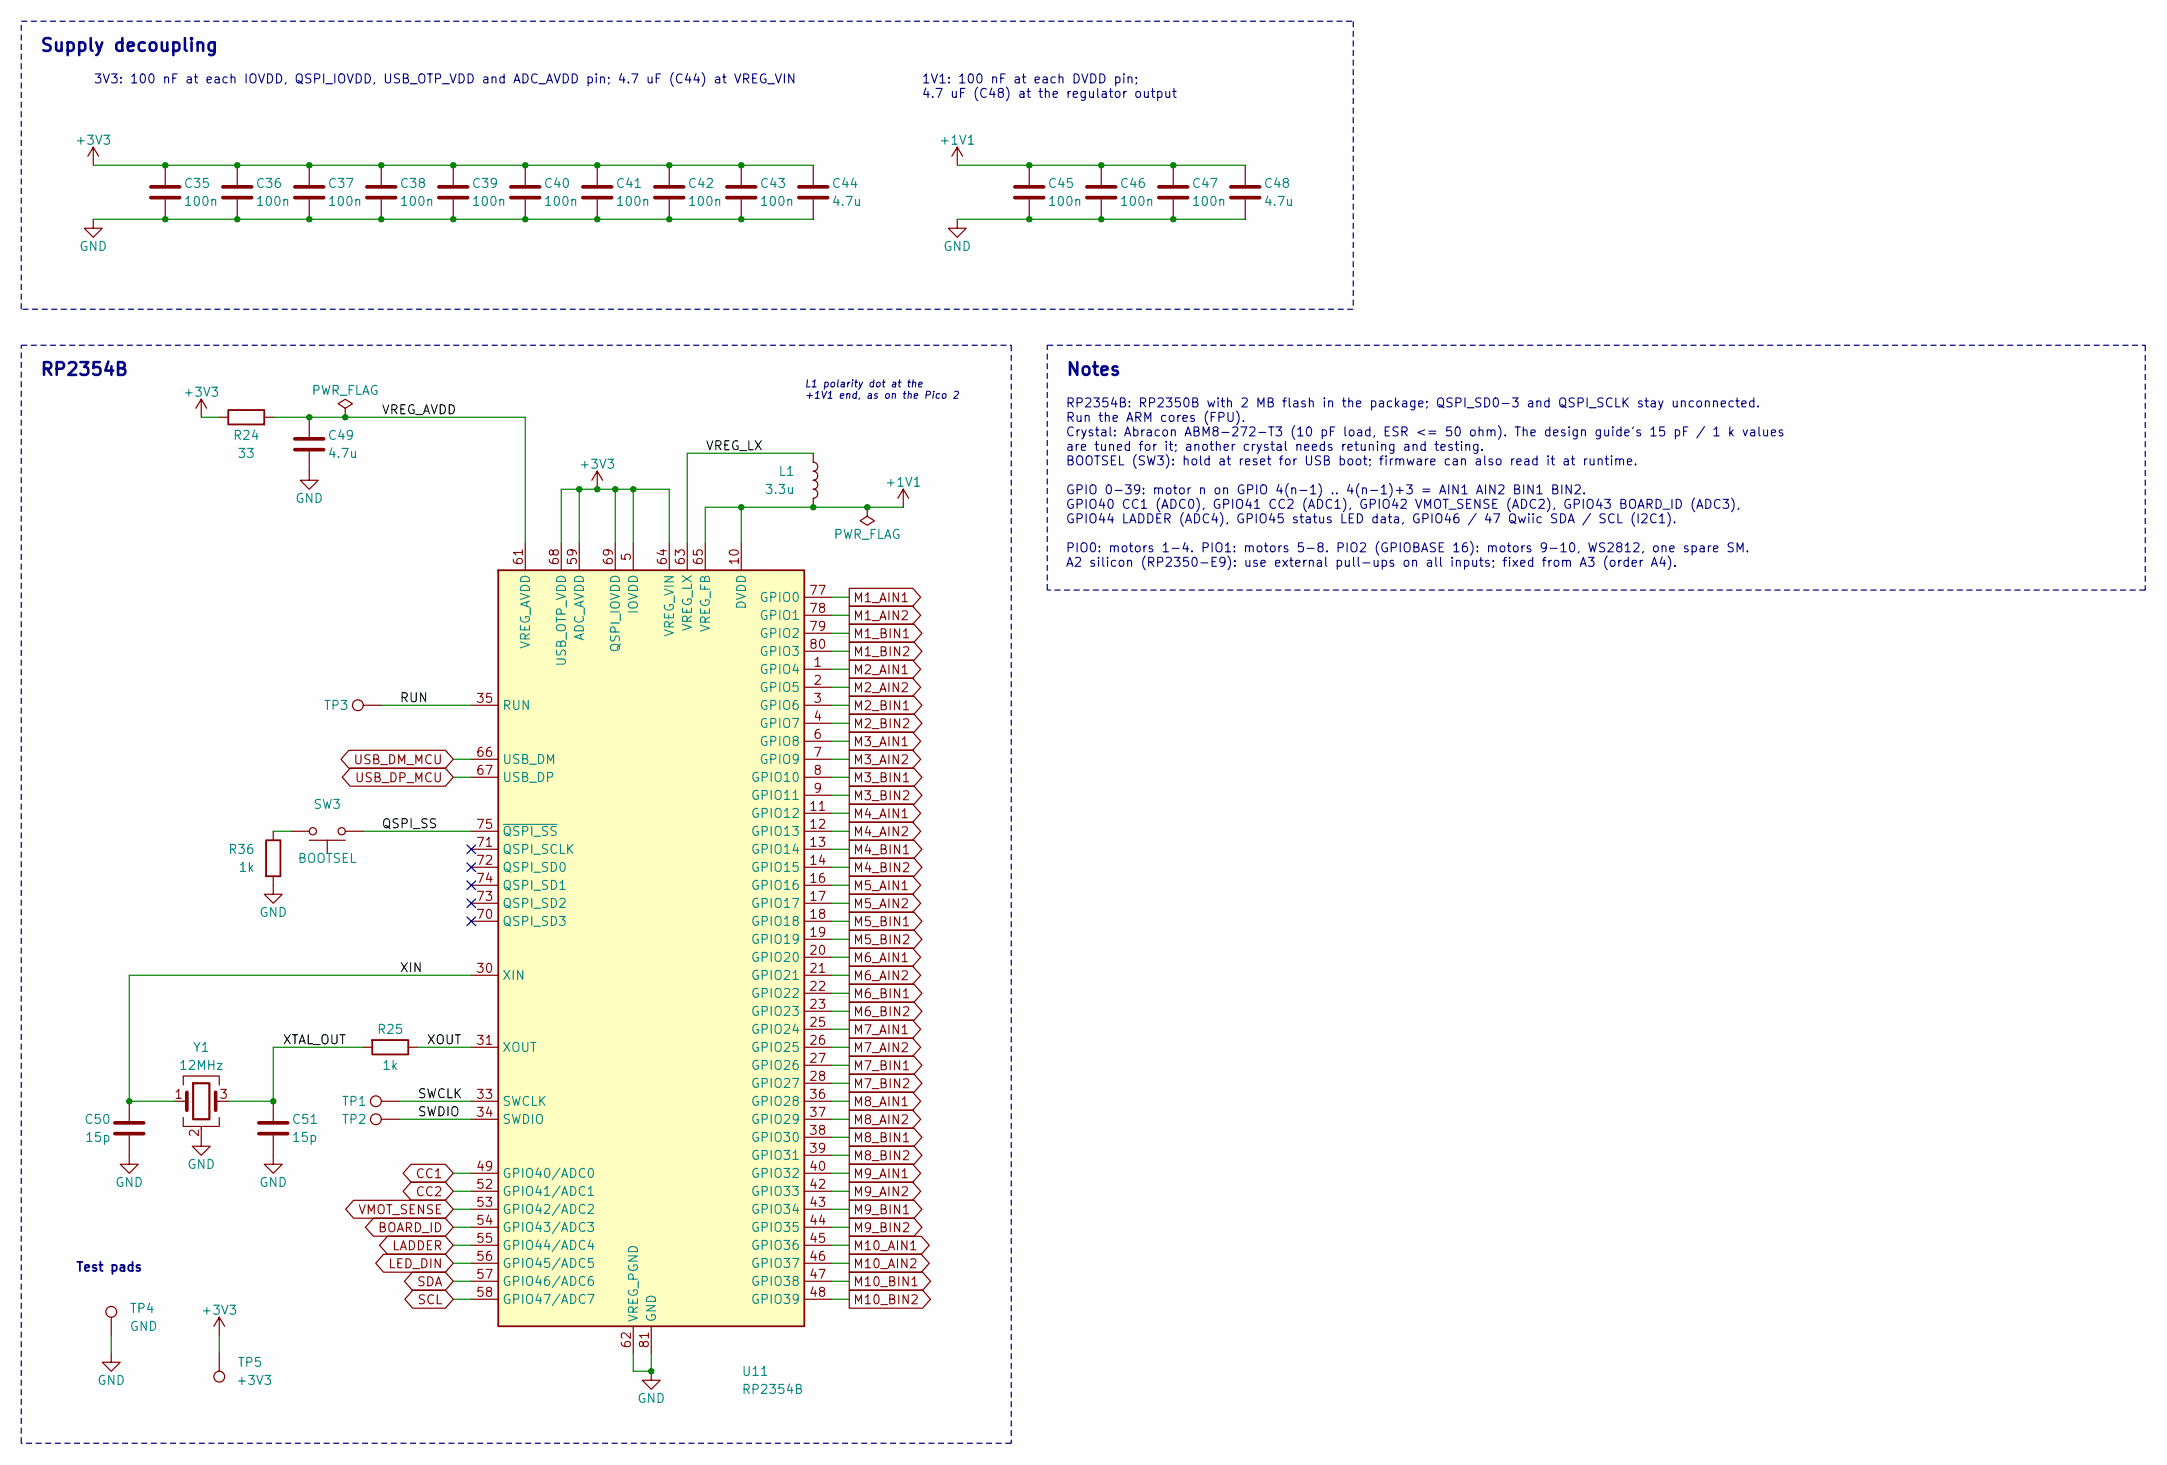
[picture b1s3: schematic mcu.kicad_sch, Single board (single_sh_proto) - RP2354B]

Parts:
C35, C36, C37, C38, C39, C40, C41, C42, C43, C45, C46, C47: 100n; C_0603_1608Metric; MPN CC0603KRX7R9BB104; LCSC C14663
C44, C48, C49: 4.7u; C_0603_1608Metric; MPN CL10A475KO8NNNC; LCSC C19666
C50, C51: 15p; C_0603_1608Metric; MPN CL10C150JB8NNNC; LCSC C1644
L1: 3.3u; L_Cenker_CKCS201610; MPN CMLW201610S3R3MST; LCSC C411344
R24: 33; R_0603_1608Metric; MPN 0603WAF330JT5E; LCSC C23140
R25, R36: 1k; R_0603_1608Metric; MPN 0603WAF1001T5E; LCSC C21190
SW3: BOOTSEL; SW_SPST_TS-1088-xR020; MPN TS-1088-AR02016; LCSC C720477
TP1: SWCLK; TestPoint_Pad_D1.0mm
TP2: SWDIO; TestPoint_Pad_D1.0mm
TP3: RUN; TestPoint_Pad_D1.0mm
TP4: GND; TestPoint_Pad_D1.0mm
TP5: +3V3; TestPoint_Pad_D1.0mm
U11: RP2354B; QFN-80-1EP_10x10mm_P0.4mm_EP3.4x3.4mm; MPN RP2354B; LCSC C39843328
Y1: 12MHz; Crystal_SMD_3225-4Pin_3.2x2.5mm; MPN ABM8-272-T3; LCSC C20625731

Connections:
+1V1: C45.1, C46.1, C47.1, C48.1, L1.2, U11.10 (DVDD), U11.32 (DVDD), U11.51 (DVDD), U11.65 (VREG_FB); also elsewhere on the board
+3V3: C35.1, C36.1, C37.1, C38.1, C39.1, C40.1, C41.1, C42.1, C43.1, C44.1, R24.1, TP5.1, U11.5 (IOVDD), U11.15 (IOVDD), U11.24 (IOVDD), U11.29 (IOVDD), U11.41 (IOVDD), U11.50 (IOVDD), U11.59 (ADC_AVDD), U11.60 (IOVDD), U11.64 (VREG_VIN), U11.68 (USB_OTP_VDD), U11.69 (QSPI_IOVDD), U11.76 (IOVDD); also elsewhere on the board
/MCU/QSPI_SS: SW3.1, U11.75 (~QSPI_SS)
/MCU/RUN: TP3.1, U11.35 (RUN)
/MCU/SWCLK: TP1.1, U11.33 (SWCLK)
/MCU/SWDIO: TP2.1, U11.34 (SWDIO)
/MCU/VREG_AVDD: C49.1, R24.2, U11.61 (VREG_AVDD)
/MCU/VREG_LX: L1.1, U11.63 (VREG_LX)
/MCU/XIN: C50.1, U11.30 (XIN), Y1.1
/MCU/XOUT: R25.1, U11.31 (XOUT)
/MCU/XTAL_OUT: C51.1, R25.2, Y1.3
BOARD_ID: U11.54 (GPIO43/ADC3); also elsewhere on the board
CC1: U11.49 (GPIO40/ADC0); also elsewhere on the board
CC2: U11.52 (GPIO41/ADC1); also elsewhere on the board
GND: C35.2, C36.2, C37.2, C38.2, C39.2, C40.2, C41.2, C42.2, C43.2, C44.2, C45.2, C46.2, C47.2, C48.2, C49.2, C50.2, C51.2, R36.2, TP4.1, U11.62 (VREG_PGND), U11.81 (GND), Y1.2 (G), Y1.4 (G); also elsewhere on the board
LADDER: U11.55 (GPIO44/ADC4); also elsewhere on the board
LED_DIN: U11.56 (GPIO45/ADC5); also elsewhere on the board
M1_AIN1: U11.77 (GPIO0); also elsewhere on the board
M1_AIN2: U11.78 (GPIO1); also elsewhere on the board
M1_BIN1: U11.79 (GPIO2); also elsewhere on the board
M1_BIN2: U11.80 (GPIO3); also elsewhere on the board
M2_AIN1: U11.1 (GPIO4); also elsewhere on the board
M2_AIN2: U11.2 (GPIO5); also elsewhere on the board
M2_BIN1: U11.3 (GPIO6); also elsewhere on the board
M2_BIN2: U11.4 (GPIO7); also elsewhere on the board
M3_AIN1: U11.6 (GPIO8); also elsewhere on the board
M3_AIN2: U11.7 (GPIO9); also elsewhere on the board
M3_BIN1: U11.8 (GPIO10); also elsewhere on the board
M3_BIN2: U11.9 (GPIO11); also elsewhere on the board
M4_AIN1: U11.11 (GPIO12); also elsewhere on the board
M4_AIN2: U11.12 (GPIO13); also elsewhere on the board
M4_BIN1: U11.13 (GPIO14); also elsewhere on the board
M4_BIN2: U11.14 (GPIO15); also elsewhere on the board
M5_AIN1: U11.16 (GPIO16); also elsewhere on the board
M5_AIN2: U11.17 (GPIO17); also elsewhere on the board
M5_BIN1: U11.18 (GPIO18); also elsewhere on the board
M5_BIN2: U11.19 (GPIO19); also elsewhere on the board
M6_AIN1: U11.20 (GPIO20); also elsewhere on the board
M6_AIN2: U11.21 (GPIO21); also elsewhere on the board
M6_BIN1: U11.22 (GPIO22); also elsewhere on the board
M6_BIN2: U11.23 (GPIO23); also elsewhere on the board
M7_AIN1: U11.25 (GPIO24); also elsewhere on the board
M7_AIN2: U11.26 (GPIO25); also elsewhere on the board
M7_BIN1: U11.27 (GPIO26); also elsewhere on the board
M7_BIN2: U11.28 (GPIO27); also elsewhere on the board
M8_AIN1: U11.36 (GPIO28); also elsewhere on the board
M8_AIN2: U11.37 (GPIO29); also elsewhere on the board
M8_BIN1: U11.38 (GPIO30); also elsewhere on the board
M8_BIN2: U11.39 (GPIO31); also elsewhere on the board
M9_AIN1: U11.40 (GPIO32); also elsewhere on the board
M9_AIN2: U11.42 (GPIO33); also elsewhere on the board
M9_BIN1: U11.43 (GPIO34); also elsewhere on the board
M9_BIN2: U11.44 (GPIO35); also elsewhere on the board
M10_AIN1: U11.45 (GPIO36); also elsewhere on the board
M10_AIN2: U11.46 (GPIO37); also elsewhere on the board
M10_BIN1: U11.47 (GPIO38); also elsewhere on the board
M10_BIN2: U11.48 (GPIO39); also elsewhere on the board
unnamed: R36.1, SW3.2
SCL: U11.58 (GPIO47/ADC7); also elsewhere on the board
SDA: U11.57 (GPIO46/ADC6); also elsewhere on the board
USB_DM_MCU: U11.66 (USB_DM); also elsewhere on the board
USB_DP_MCU: U11.67 (USB_DP); also elsewhere on the board
VMOT_SENSE: U11.53 (GPIO42/ADC2); also elsewhere on the board

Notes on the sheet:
RP2354B
L1 polarity dot at the +1V1 end, as on the Pico 2
Supply decoupling
3V3: 100 nF at each IOVDD, QSPI_IOVDD, USB_OTP_VDD and ADC_AVDD pin; 4.7 uF (C44) at VREG_VIN
1V1: 100 nF at each DVDD pin; 4.7 uF (C48) at the regulator output
Test pads
Notes
RP2354B: RP2350B with 2 MB flash in the package; QSPI_SD0-3 and QSPI_SCLK stay unconnected. Run the ARM cores (FPU). Crystal: Abracon ABM8-272-T3 (10 pF load, ESR <= 50 ohm). The design guide's 15 pF / 1 k values are tuned for it; another crystal needs retuning and testing. BOOTSEL (SW3): hold at r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
